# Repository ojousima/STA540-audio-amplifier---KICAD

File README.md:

STA540-audio-amplifier---KICAD
==============================

STA540 2 bridged channel audio amplifier, operates in class AB, 12->20 V operating voltage.

## License

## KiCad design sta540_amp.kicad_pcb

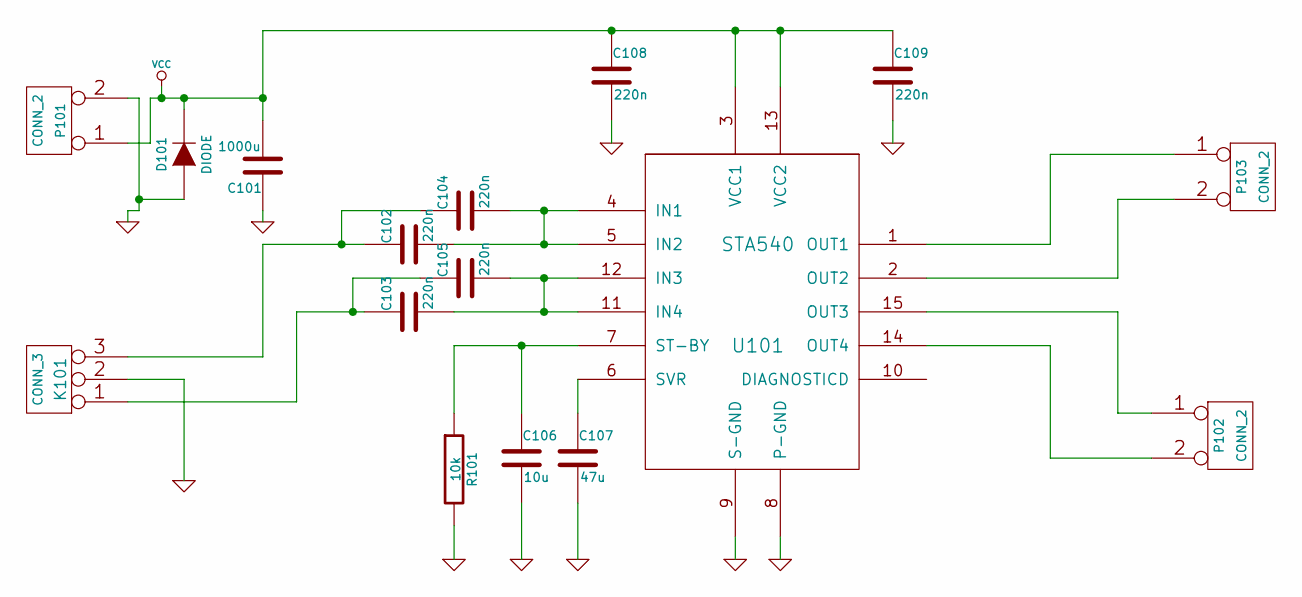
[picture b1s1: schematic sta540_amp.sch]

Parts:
C101: 1000u
C102, C103, C104, C105, C108, C109: 220n
C106: 10u
C107: 47u
D101: DIODE
K101: CONN_3
P101, P102, P103: CONN_2
R101: 10k
U101: STA540

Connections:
GND: C101.1, C106.2, C107.2, C108.2, C109.2, D101.1 (A), K101.2 (PM), P101.2 (PM), R101.2, U101.8 (P-GND), U101.9 (S-GND)
unnamed: C106.1, R101.1, U101.7 (ST-BY)
unnamed: C107.1, U101.6 (SVR)
unnamed: C103.2, C105.2, U101.11 (IN4), U101.12 (IN3)
unnamed: P102.1, U101.15 (OUT3)
unnamed: P103.1, U101.1 (OUT1)
unnamed: P103.2 (PM), U101.2 (OUT2)
unnamed: P102.2 (PM), U101.14 (OUT4)
unnamed: C102.2, C104.2, U101.4 (IN1), U101.5 (IN2)
unnamed: C103.1, C105.1, K101.1
unnamed: C102.1, C104.1, K101.3
VCC: C101.2, C108.1, C109.1, D101.2 (K), P101.1, U101.3 (VCC1), U101.13 (VCC2)

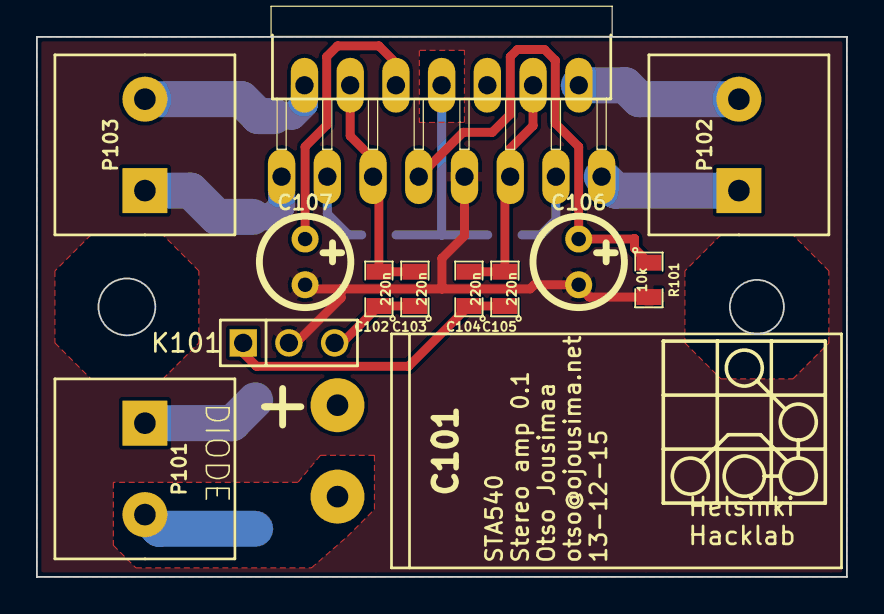
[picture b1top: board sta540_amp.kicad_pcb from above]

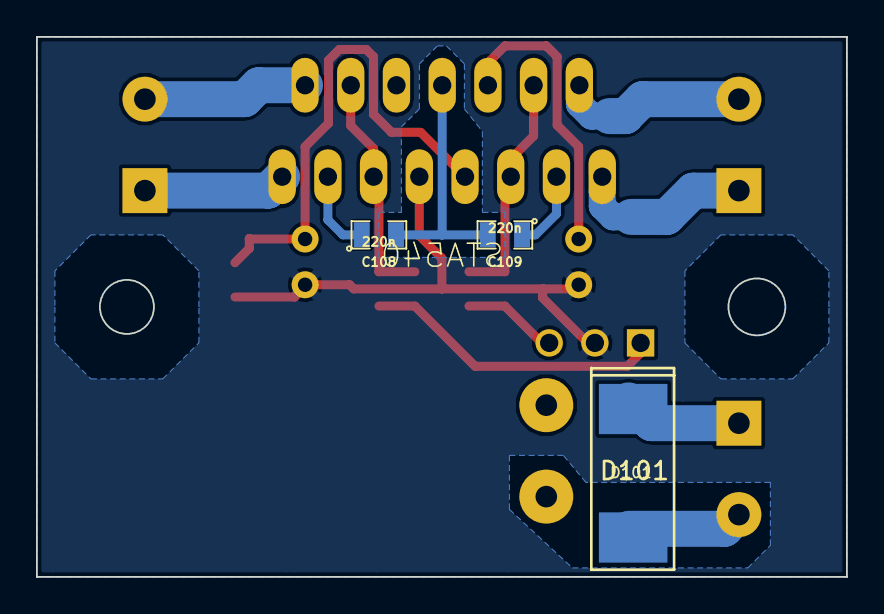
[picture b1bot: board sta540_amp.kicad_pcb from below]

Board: 4 copper layers, 45.0 x 30.0 mm, 16 parts (3 on the bottom side), 12 nets.

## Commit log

2014-10-04 First version
2018-04-17 Add license scan report and status
